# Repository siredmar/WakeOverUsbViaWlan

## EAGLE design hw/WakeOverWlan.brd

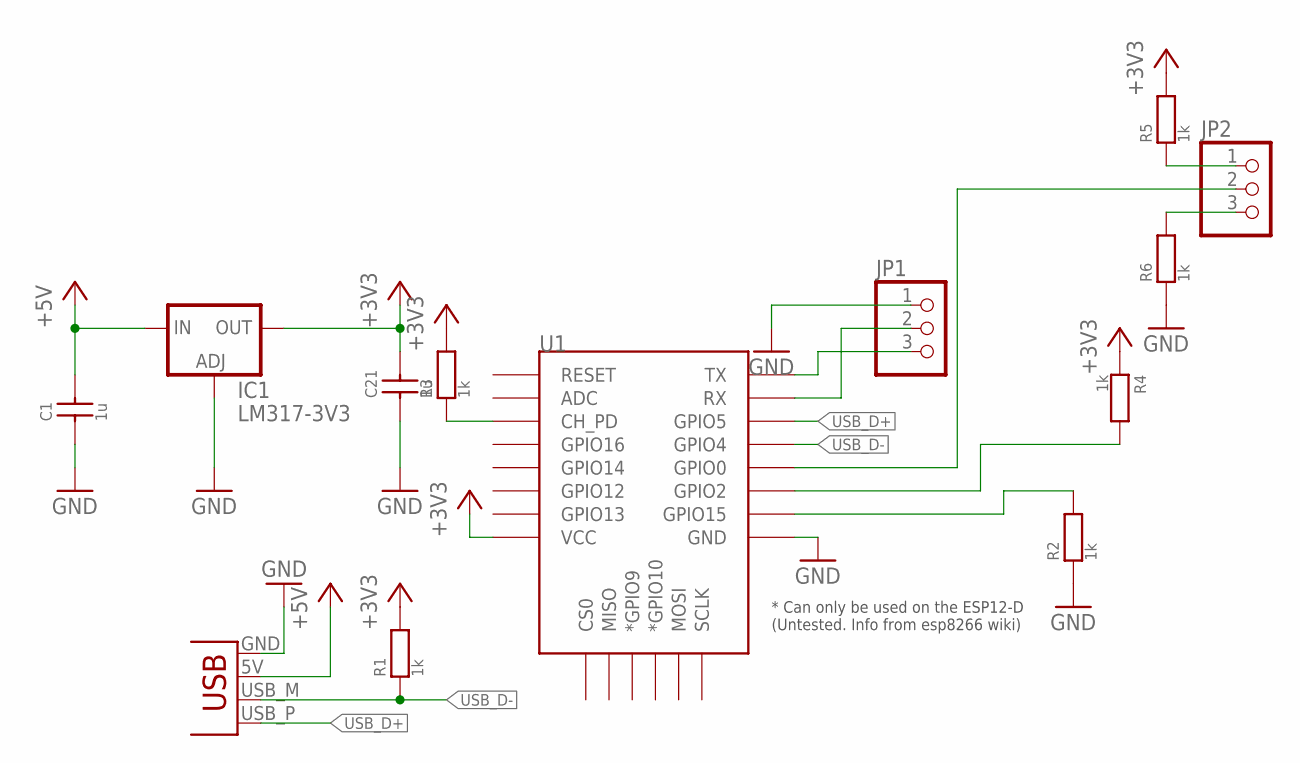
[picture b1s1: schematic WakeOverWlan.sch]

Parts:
C1, C21: 1u; C0805
IC1: LM317-3V3; SOT223
JP1, JP2: PINHD-1X3; 1X03
R1, R2, R3, R4, R5, R6: 1k; R0603
U1: ESP12ESMD; ESP12E-SMD
X1: USBPCB; USB-A-PCB

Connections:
+3V3: C21.2, IC1.4 (OUT), R1.2, R3.2, R4.1, R5.2, U1.VCC
+5V: C1.2, IC1.3 (IN), X1.5V (VBUS)
GND: C1.1, C21.1, IC1.1 (ADJ), JP1.1, R2.1, R6.1, U1.GND, X1.GND
unnamed: R2.2, U1.GPIO15
unnamed: R3.1, U1.CH_PD
unnamed: R4.2, U1.GPIO2
unnamed: JP2.2, U1.GPIO0
unnamed: JP2.1, R5.1
unnamed: JP2.3, R6.2
RX: JP1.2, U1.RXD0 (RX)
TX: JP1.3, U1.TXD0 (TX)
USB_D+: U1.GPIO5, X1.USB_P (D+)
USB_D-: R1.1, U1.GPIO4, X1.USB_M (D-)

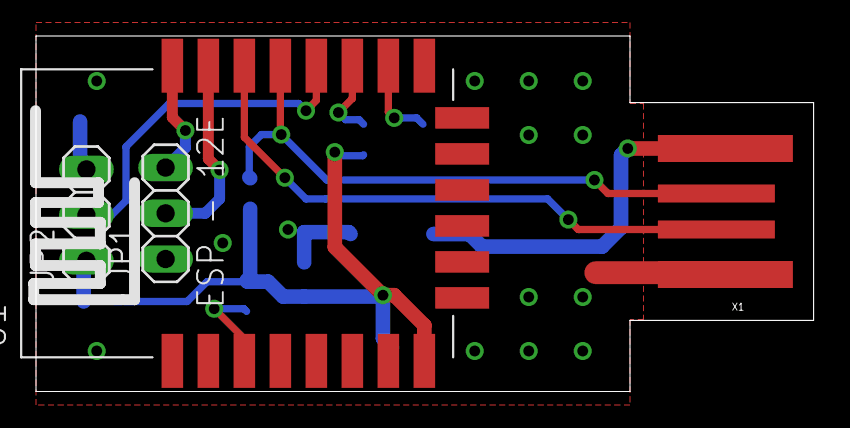
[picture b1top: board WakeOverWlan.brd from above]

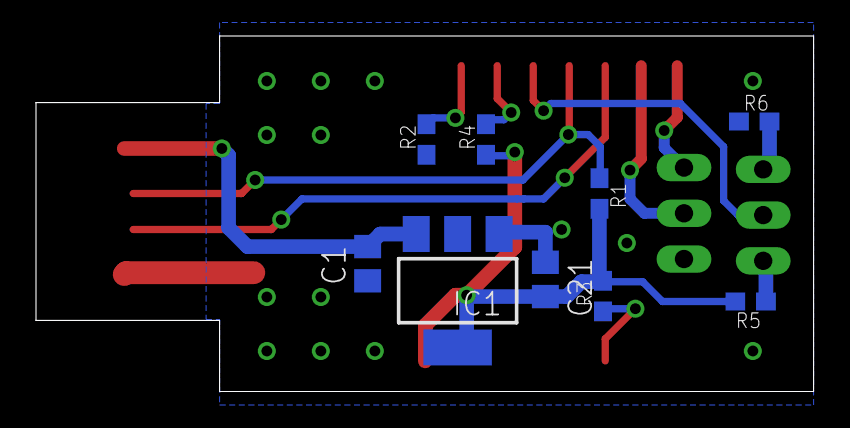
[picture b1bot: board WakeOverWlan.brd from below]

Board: 2 copper layers, 43.2 x 19.8 mm, 13 parts (9 on the bottom side), 13 nets.

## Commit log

2017-02-20 Initial commit. SW working. HW initial commit
